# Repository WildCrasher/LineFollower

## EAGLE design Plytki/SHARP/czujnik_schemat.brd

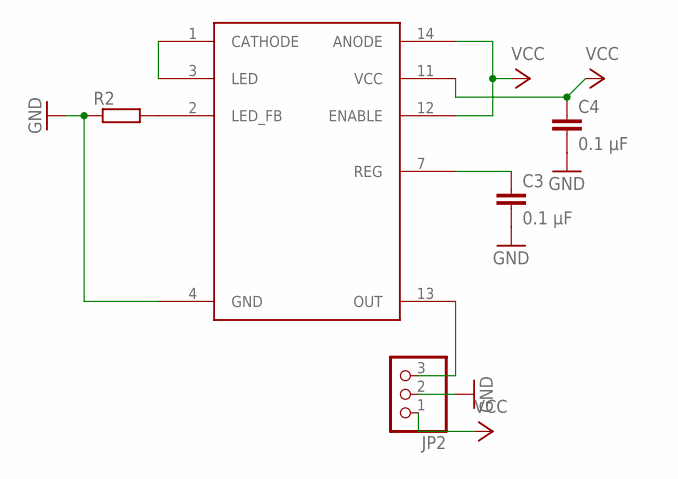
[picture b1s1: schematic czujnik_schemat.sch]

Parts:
C3, C4: 0.1 μF; C025-025X050
JP2: PINHD-1X3; 1X03
R2: R-EU_0204/5; 0204/5
U$2: GP2Y0D810Z0F; LP16PIN

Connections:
GND: C3.2, C4.2, JP2.2, R2.1, U$2.4 (GND)
unnamed: R2.2, U$2.2 (LED_FB)
unnamed: C3.1, U$2.7 (REG)
unnamed: U$2.1 (CATHODE), U$2.3 (LED)
unnamed: JP2.3, U$2.13 (OUT)
VCC: C4.1, JP2.1, U$2.11 (VCC), U$2.12 (ENABLE), U$2.14 (ANODE)

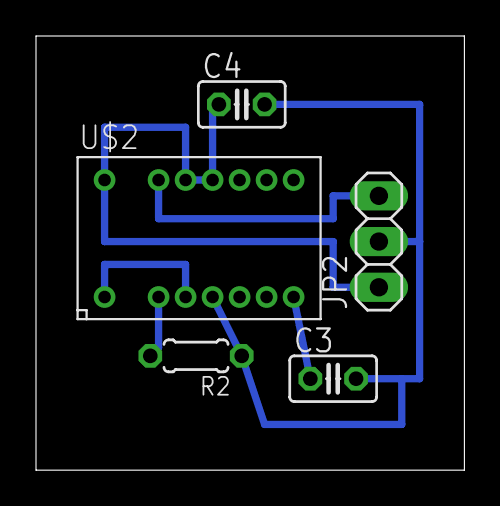
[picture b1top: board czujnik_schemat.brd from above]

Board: 2 copper layers, 23.8 x 24.1 mm, 5 parts (0 on the bottom side), 6 nets.

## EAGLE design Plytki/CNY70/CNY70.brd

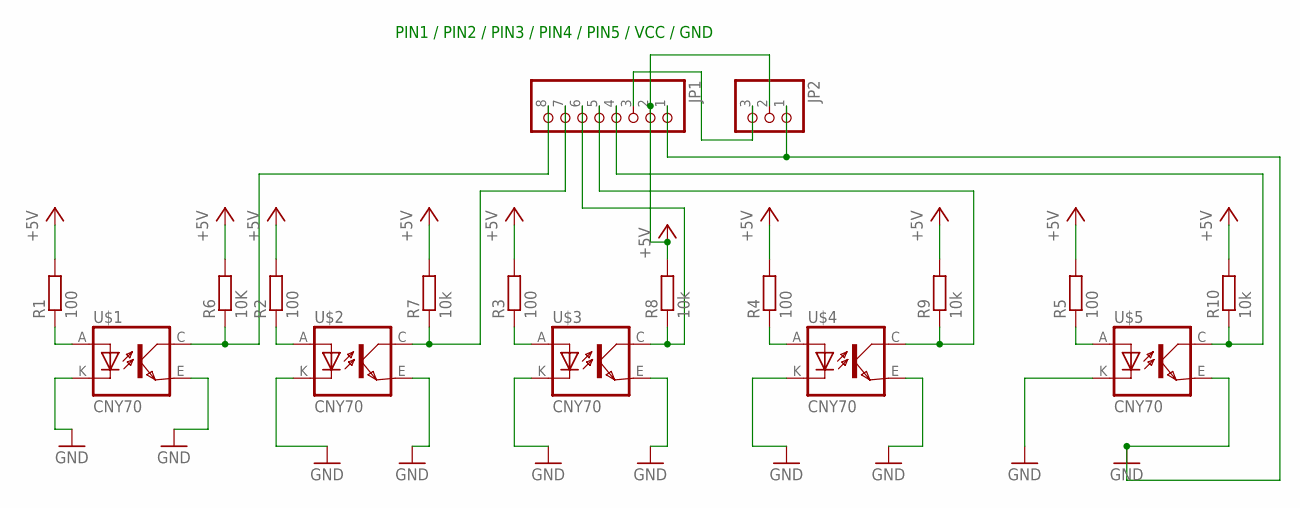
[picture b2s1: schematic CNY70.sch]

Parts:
JP1: PINHD-1X8; 1X08
JP2: PINHD-1X3; 1X03
R1, R2, R3, R4, R5: 100; 0309/12
R6: 10K; 0309/12
R7, R8, R9, R10: 10k; 0309/12
U$1, U$2, U$3, U$4, U$5: CNY70; 4

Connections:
+5V: JP1.2, JP2.2, R1.2, R2.2, R3.2, R4.2, R5.2, R6.2, R7.2, R8.2, R9.2, R10.2
GND: JP1.1, JP2.1, U$1.E (EMI), U$1.K (C), U$2.E (EMI), U$2.K (C), U$3.E (EMI), U$3.K (C), U$4.E (EMI), U$4.K (C), U$5.E (EMI), U$5.K (C)
unnamed: R1.1, U$1.A
unnamed: R2.1, U$2.A
unnamed: R3.1, U$3.A
unnamed: R4.1, U$4.A
unnamed: R5.1, U$5.A
unnamed: JP1.8, R6.1, U$1.C (COL)
unnamed: JP1.7, R7.1, U$2.C (COL)
unnamed: JP1.6, R8.1, U$3.C (COL)
unnamed: JP1.3, JP2.3
unnamed: JP1.4, R10.1, U$5.C (COL)
unnamed: JP1.5, R9.1, U$4.C (COL)

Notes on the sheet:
PIN1 / PIN2 / PIN3 / PIN4 / PIN5 / VCC / GND

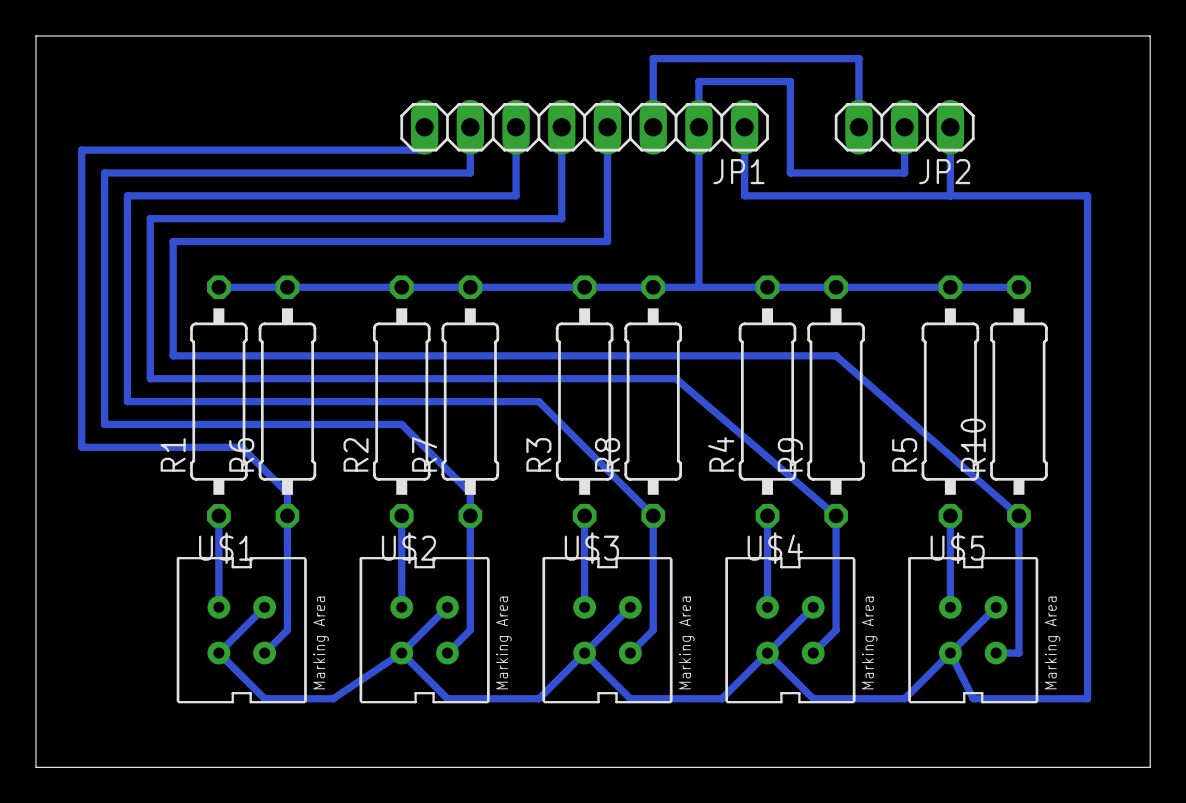
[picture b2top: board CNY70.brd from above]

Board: 2 copper layers, 61.9 x 40.6 mm, 17 parts (0 on the bottom side), 13 nets.

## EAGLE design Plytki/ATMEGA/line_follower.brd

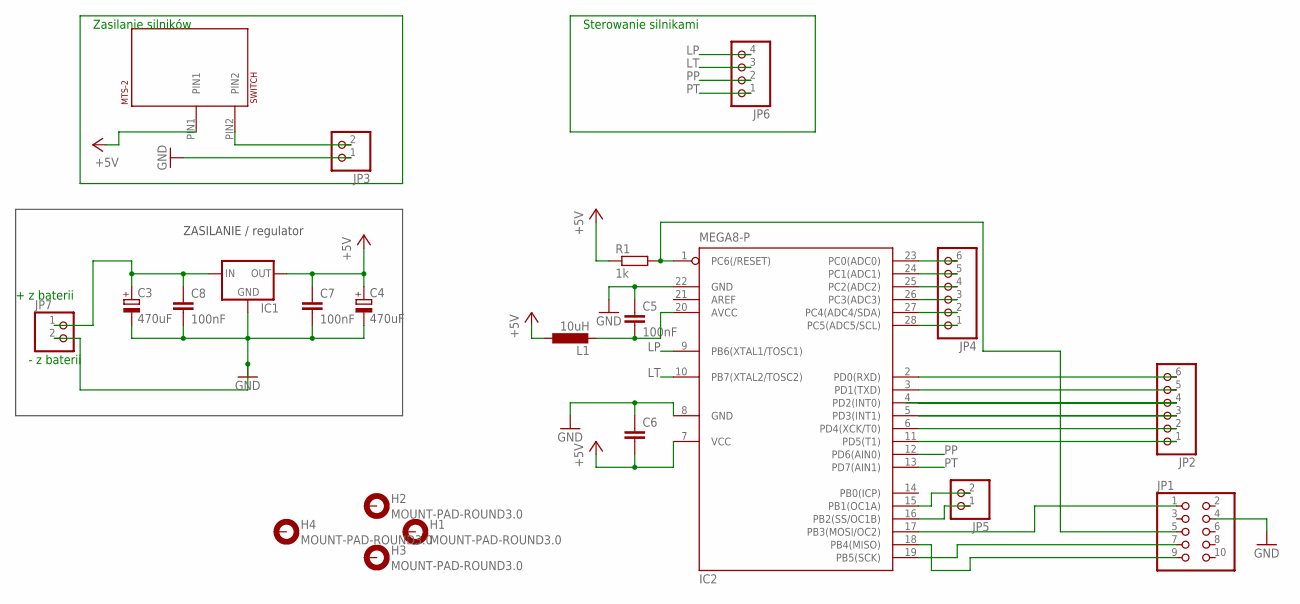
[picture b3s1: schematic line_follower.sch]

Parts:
C3, C4: 470uF; E2,5-6
C5, C7, C8: 100nF; C025-025X050
C6: C-EU025-025X050; C025-025X050
H1, H2, H3, H4: MOUNT-PAD-ROUND3.0; 3,0-PAD
IC1: 78XXS
IC2: MEGA8-P; DIL28-3
JP1: PINHD-2X5; 2X05
JP2, JP4: PINHD-1X6; 1X06
JP3, JP5, JP7: PINHD-1X2; 1X02
JP6: PINHD-1X4; 1X04
L1: 10uH; 0207/5V
MTS-2: SWITCH; MTS-2_SWITCH
R1: 1k; 0204/5

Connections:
+5V: C4.+, C6.2, C7.1, IC1.OUT, IC2.7 (VCC), L1.1, MTS-2.PIN1, R1.1
GND: C3.-, C4.-, C5.1, C6.1, C7.2, C8.2, IC1.GND, IC2.8 (GND), IC2.22 (GND), JP1.4, JP3.1, JP7.2
LP: IC2.9 (PB6(XTAL1/TOSC1)), JP6.4
LT: IC2.10 (PB7(XTAL2/TOSC2)), JP6.3
unnamed: C5.2, IC2.20 (AVCC), L1.2
unnamed: IC2.23 (PC0(ADC0)), JP4.6
unnamed: IC2.1 (PC6(/RESET)), JP1.5, R1.2
unnamed: IC2.17 (PB3(MOSI/OC2)), JP1.1
unnamed: IC2.18 (PB4(MISO)), JP1.9
unnamed: IC2.2 (PD0(RXD)), JP2.6
unnamed: IC2.19 (PB5(SCK)), JP1.7
unnamed: IC2.3 (PD1(TXD)), JP2.5
unnamed: IC2.4 (PD2(INT0)), JP2.4
unnamed: IC2.5 (PD3(INT1)), JP2.3
unnamed: IC2.6 (PD4(XCK/T0)), JP2.2
unnamed: IC2.11 (PD5(T1)), JP2.1
unnamed: C3.+, C8.1, IC1.IN, JP7.1
unnamed: IC2.24 (PC1(ADC1)), JP4.5
unnamed: IC2.25 (PC2(ADC2)), JP4.4
unnamed: IC2.26 (PC3(ADC3)), JP4.3
unnamed: IC2.27 (PC4(ADC4/SDA)), JP4.2
unnamed: IC2.28 (PC5(ADC5/SCL)), JP4.1
unnamed: IC2.15 (PB1(OC1A)), JP5.2
unnamed: IC2.16 (PB2(SS/OC1B)), JP5.1
unnamed: JP3.2, MTS-2.PIN2
PP: IC2.12 (PD6(AIN0)), JP6.2
PT: IC2.13 (PD7(AIN1)), JP6.1

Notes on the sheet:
ZASILANIE / regulator
Zasilanie silników
Sterowanie silnikami
+ z baterii
- z baterii

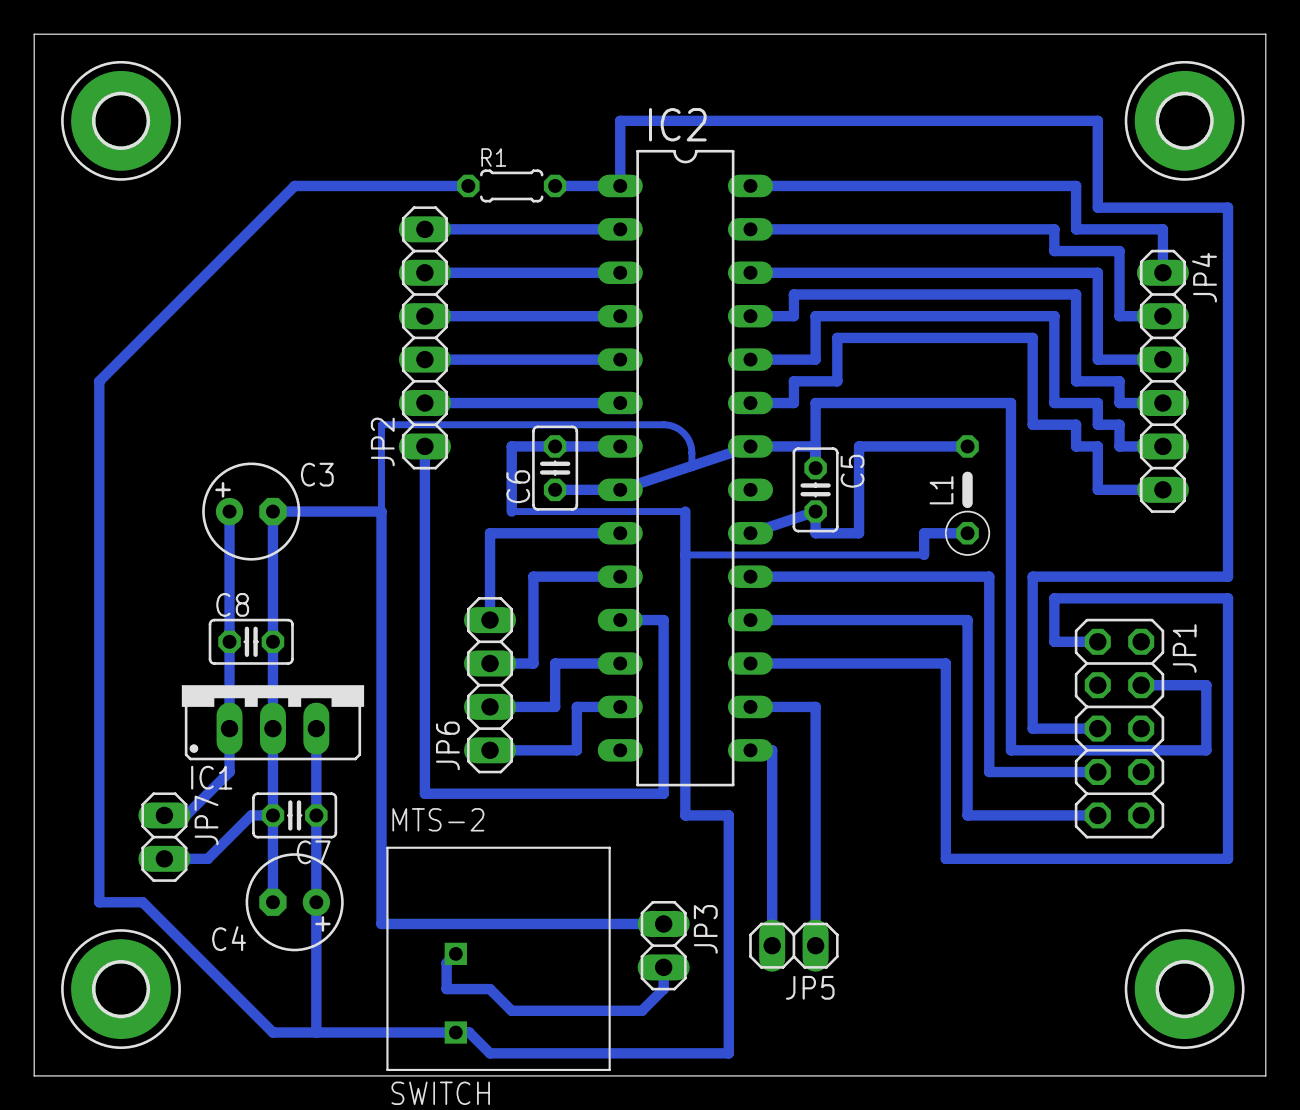
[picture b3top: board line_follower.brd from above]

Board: 2 copper layers, 72.1 x 61.0 mm, 22 parts (0 on the bottom side), 27 nets.

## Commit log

2017-06-10 Project done
2017-06-10 test pdf
2017-06-10 DTR- dokumentacja, kod
2017-06-10 Revert "DTR- dokumentacja, kod"
    This reverts commit e6b6094d8b0bc0e170c045d06224e803add3bae5.
2017-06-10 Projekty plytek
2017-06-10 Ostateczne projekty plytek
2017-06-10 Bez czujnika SHARP'a
